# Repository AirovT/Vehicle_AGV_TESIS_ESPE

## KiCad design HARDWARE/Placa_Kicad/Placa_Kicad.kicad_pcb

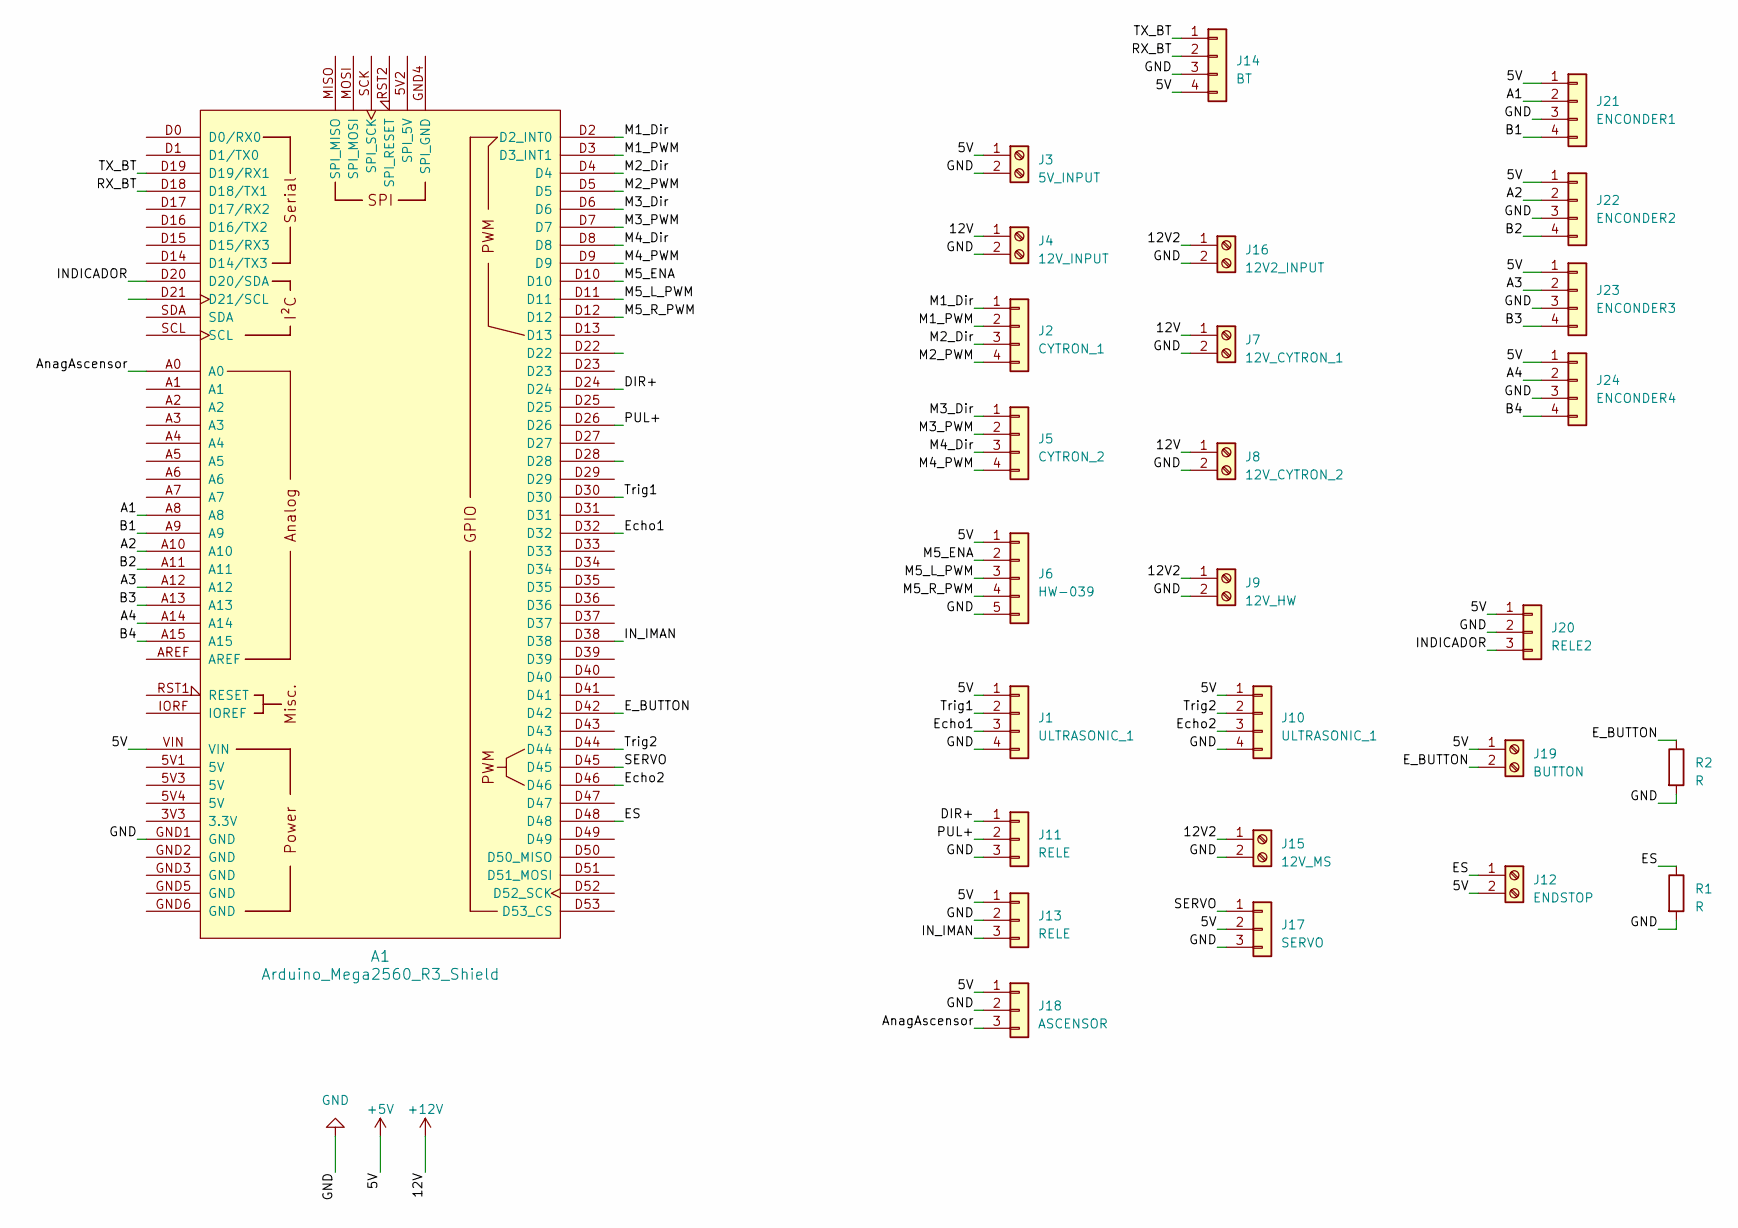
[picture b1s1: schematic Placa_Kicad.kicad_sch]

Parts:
A1: Arduino_Mega2560_R3_Shield
J1, J10: ULTRASONIC_1; JST_EH_B4B-EH-A_1x04_P2.50mm_Vertical
J2: CYTRON_1; JST_EH_B4B-EH-A_1x04_P2.50mm_Vertical
J3: 5V_INPUT; TerminalBlock_bornier-2_P5.08mm
J4: 12V_INPUT; TerminalBlock_bornier-2_P5.08mm
J5: CYTRON_2; JST_EH_B4B-EH-A_1x04_P2.50mm_Vertical
J6: HW-039; JST_EH_B5B-EH-A_1x05_P2.50mm_Vertical
J7: 12V_CYTRON_1; TerminalBlock_4Ucon_1x02_P3.50mm_Horizontal
J8: 12V_CYTRON_2; TerminalBlock_4Ucon_1x02_P3.50mm_Horizontal
J9: 12V_HW; TerminalBlock_4Ucon_1x02_P3.50mm_Horizontal
J11, J13: RELE; JST_EH_B3B-EH-A_1x03_P2.50mm_Vertical
J12: ENDSTOP; TerminalBlock_4Ucon_1x02_P3.50mm_Horizontal
J14: BT; JST_EH_B4B-EH-A_1x04_P2.50mm_Vertical
J15: 12V_MS; TerminalBlock_4Ucon_1x02_P3.50mm_Horizontal
J16: 12V2_INPUT; TerminalBlock_bornier-2_P5.08mm
J17: SERVO; JST_EH_B3B-EH-A_1x03_P2.50mm_Vertical
J18: ASCENSOR; JST_EH_B3B-EH-A_1x03_P2.50mm_Vertical
J19: BUTTON; TerminalBlock_4Ucon_1x02_P3.50mm_Horizontal
J20: RELE2; JST_EH_B3B-EH-A_1x03_P2.50mm_Vertical
J21: ENCONDER1; JST_EH_B4B-EH-A_1x04_P2.50mm_Vertical
J22: ENCONDER2; JST_EH_B4B-EH-A_1x04_P2.50mm_Vertical
J23: ENCONDER3; JST_EH_B4B-EH-A_1x04_P2.50mm_Vertical
J24: ENCONDER4; JST_EH_B4B-EH-A_1x04_P2.50mm_Vertical
R1, R2: R; R_Axial_DIN0204_L3.6mm_D1.6mm_P7.62mm_Horizontal

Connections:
+5V: A1.VIN, J1.1, J3.1, J6.1, J10.1, J12.2, J13.1, J14.4, J17.2, J18.1, J19.1, J20.1, J21.1, J22.1, J23.1, J24.1
+12V: J4.1, J7.1, J8.1
/12V2: J9.1, J15.1, J16.1
/A1: A1.A8, J21.2
/A2: A1.A10, J22.2
/A3: A1.A12, J23.2
/A4: A1.A14, J24.2
/AnagAscensor: A1.A0, J18.3
/B1: A1.A9, J21.4
/B2: A1.A11, J22.4
/B3: A1.A13, J23.4
/B4: A1.A15, J24.4
/DIR+: A1.D24, J11.1
/ES: A1.D48, J12.1, R1.1
/E_BUTTON: A1.D42, J19.2, R2.1
/Echo1: A1.D32, J1.3
/Echo2: A1.D46, J10.3
/INDICADOR: A1.D20 (D20/SDA), J20.3
/IN_IMAN: A1.D38, J13.3
/M1_Dir: A1.D2 (D2_INT0), J2.1
/M1_PWM: A1.D3 (D3_INT1), J2.2
/M2_Dir: A1.D4, J2.3
/M2_PWM: A1.D5, J2.4
/M3_Dir: A1.D6, J5.1
/M3_PWM: A1.D7, J5.2
/M4_Dir: A1.D8, J5.3
/M4_PWM: A1.D9, J5.4
/M5_ENA: A1.D10, J6.2
/M5_L_PWM: A1.D11, J6.3
/M5_R_PWM: A1.D12, J6.4
/PUL+: A1.D26, J11.2
/RX_BT: A1.D18 (D18/TX1), J14.2
/SERVO: A1.D45, J17.1
/TX_BT: A1.D19 (D19/RX1), J14.1
/Trig1: A1.D30, J1.2
/Trig2: A1.D44, J10.2
GND: A1.GND1 (GND), A1.GND2 (GND), A1.GND3 (GND), A1.GND5 (GND), A1.GND6 (GND), J1.4, J3.2, J4.2, J6.5, J7.2, J8.2, J9.2, J10.4, J11.3, J13.2, J14.3, J15.2, J16.2, J17.3, J18.2, J20.2, J21.3, J22.3, J23.3, J24.3, R1.2, R2.2

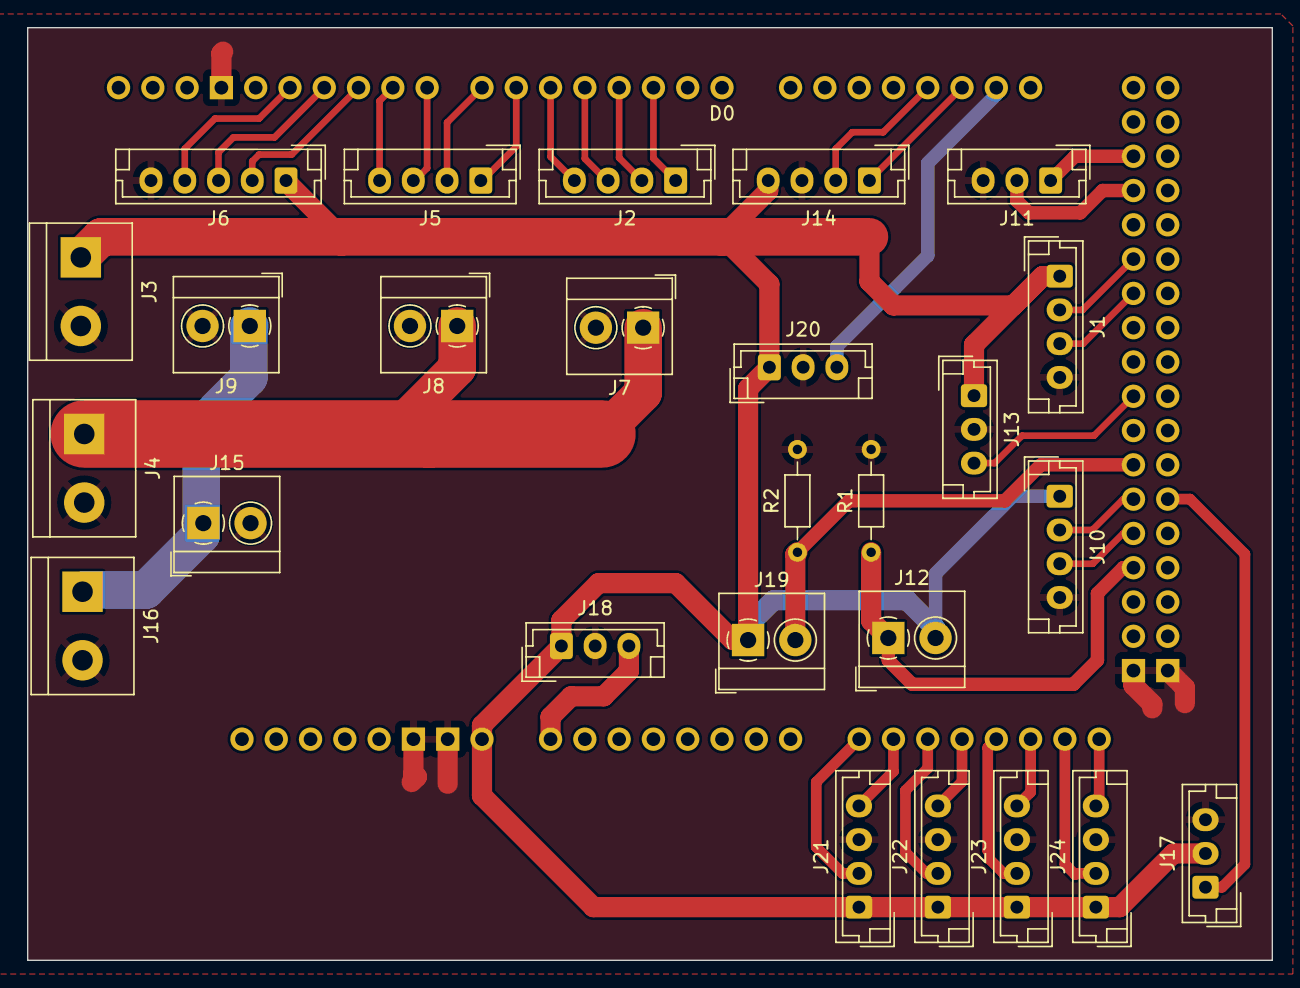
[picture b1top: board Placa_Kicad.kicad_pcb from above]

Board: 2 copper layers, 92.2 x 69.1 mm, 27 parts (0 on the bottom side), 37 nets.

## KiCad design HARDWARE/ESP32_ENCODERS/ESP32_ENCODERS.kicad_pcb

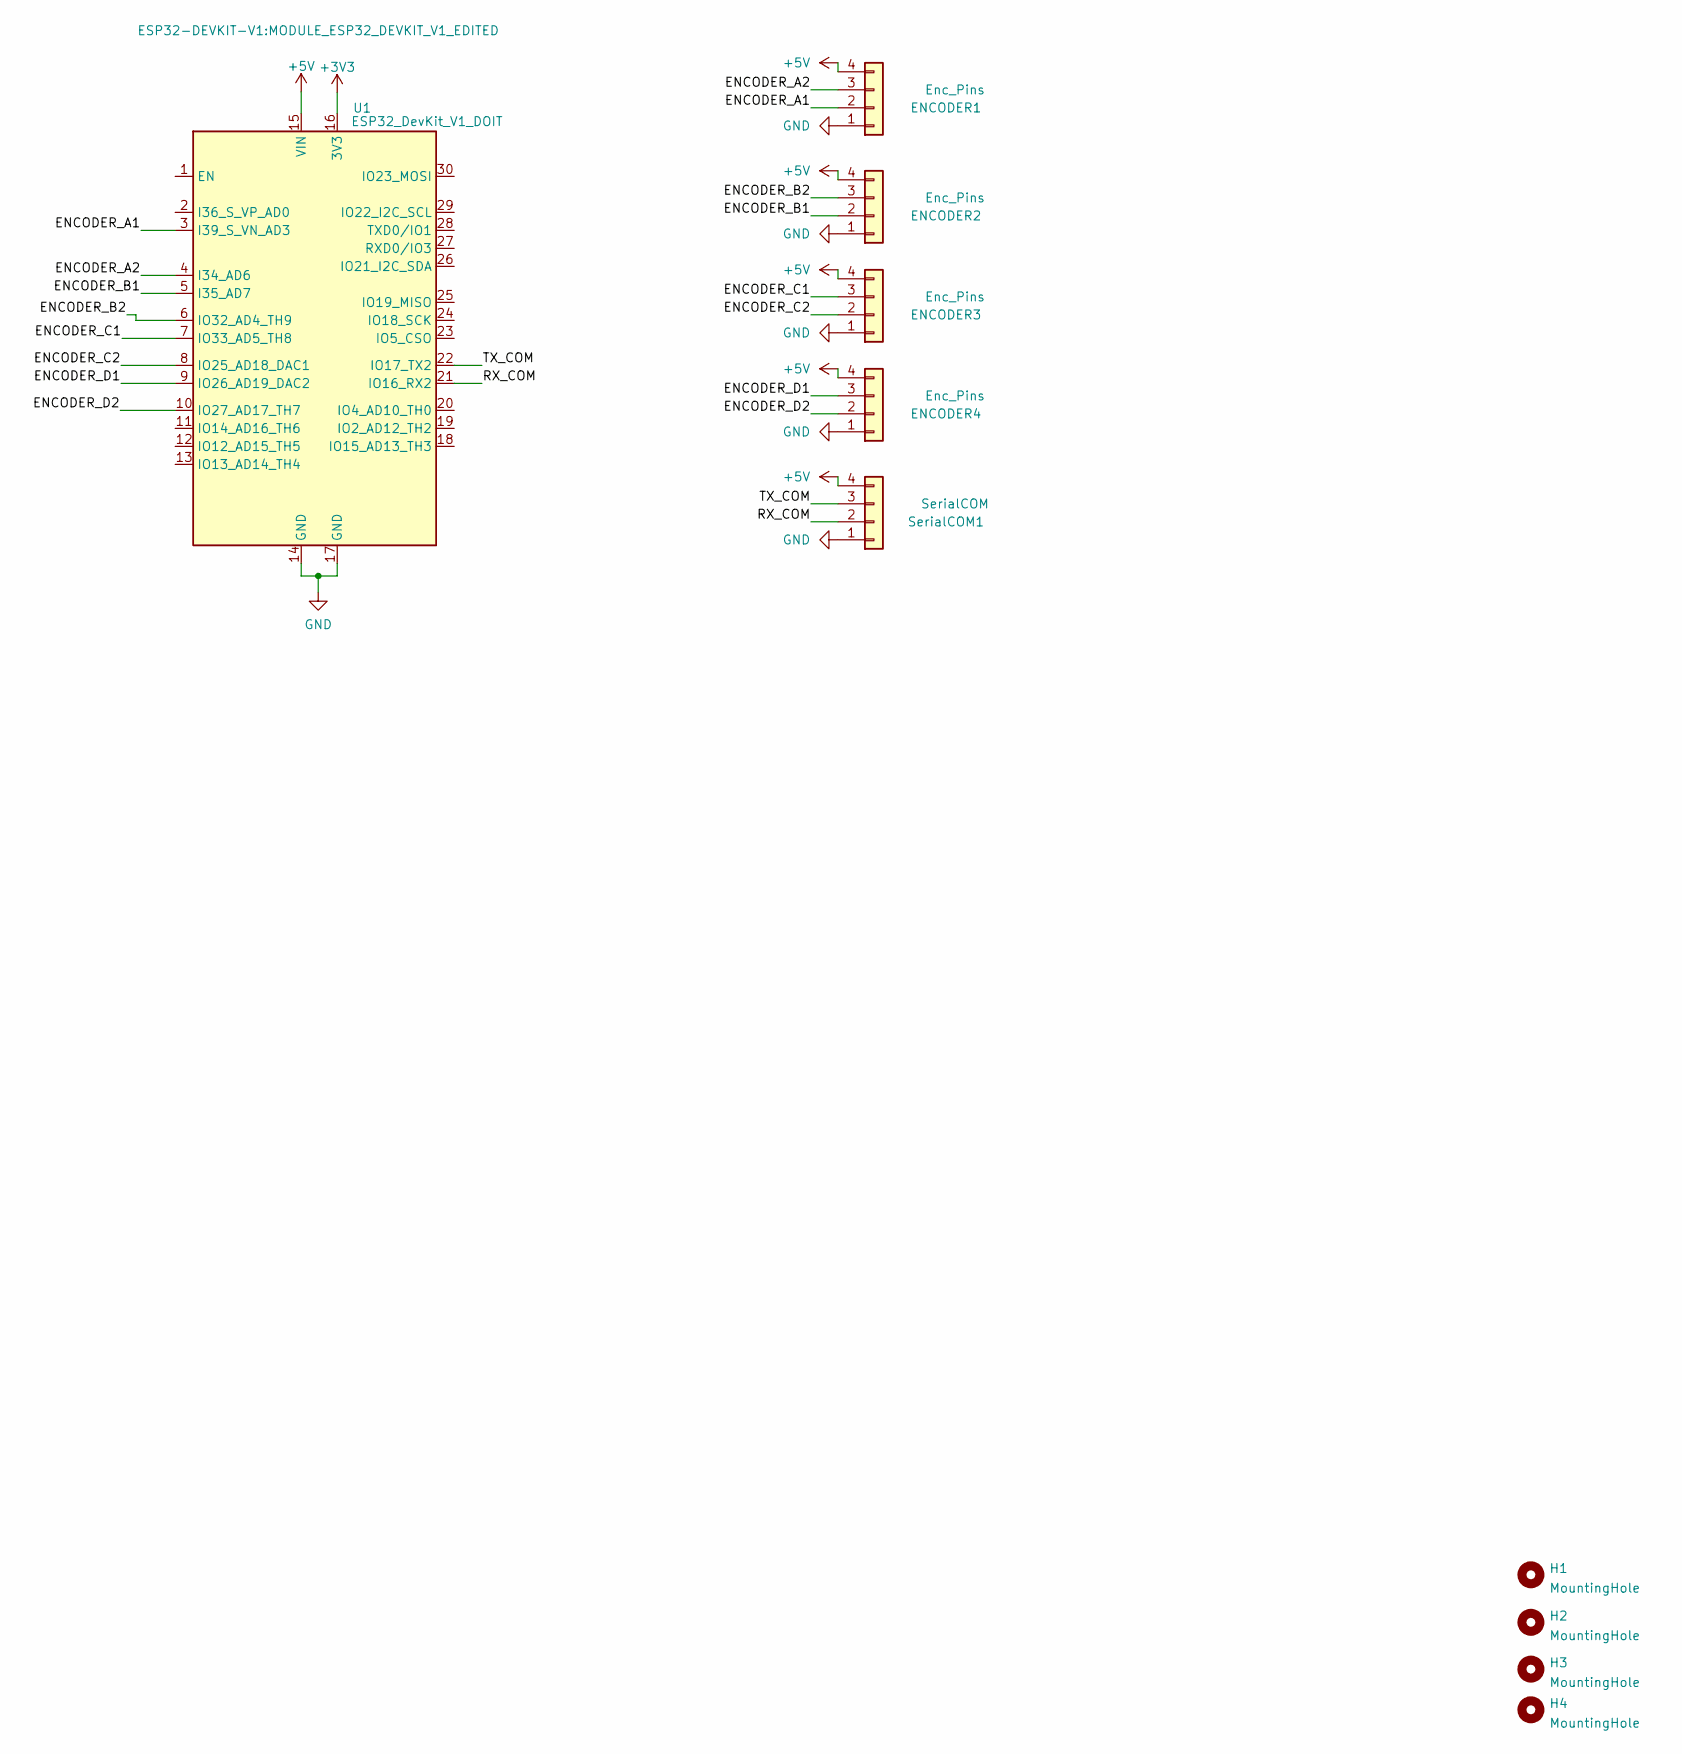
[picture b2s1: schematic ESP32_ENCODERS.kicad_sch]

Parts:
ENCODER1, ENCODER2, ENCODER3, ENCODER4: Enc_Pins; JST_EH_S4B-EH_1x04_P2.50mm_Horizontal
H1, H2, H3, H4: MountingHole; MountingHole_2.2mm_M2_DIN965_Pad
SerialCOM1: SerialCOM; JST_XA_B04B-XASK-1_1x04_P2.50mm_Vertical
U1: ESP32_DevKit_V1_DOIT; MODULE_ESP32_DEVKIT_V1_EDITED

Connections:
+3V3: U1.16 (3V3)
+5V: ENCODER1.4, ENCODER2.4, ENCODER3.4, ENCODER4.4, SerialCOM1.4, U1.15 (VIN)
/ENCODER_A1: ENCODER1.2, U1.3 (I39_S_VN_AD3)
/ENCODER_A2: ENCODER1.3, U1.4 (I34_AD6)
/ENCODER_B1: ENCODER2.2, U1.5 (I35_AD7)
/ENCODER_B2: ENCODER2.3, U1.6 (IO32_AD4_TH9)
/ENCODER_C1: ENCODER3.3, U1.7 (IO33_AD5_TH8)
/ENCODER_C2: ENCODER3.2, U1.8 (IO25_AD18_DAC1)
/ENCODER_D1: ENCODER4.3, U1.9 (IO26_AD19_DAC2)
/ENCODER_D2: ENCODER4.2, U1.10 (IO27_AD17_TH7)
/RX_COM: SerialCOM1.2, U1.21 (IO16_RX2)
/TX_COM: SerialCOM1.3, U1.22 (IO17_TX2)
GND: ENCODER1.1, ENCODER2.1, ENCODER3.1, ENCODER4.1, SerialCOM1.1, U1.14 (GND), U1.17 (GND)

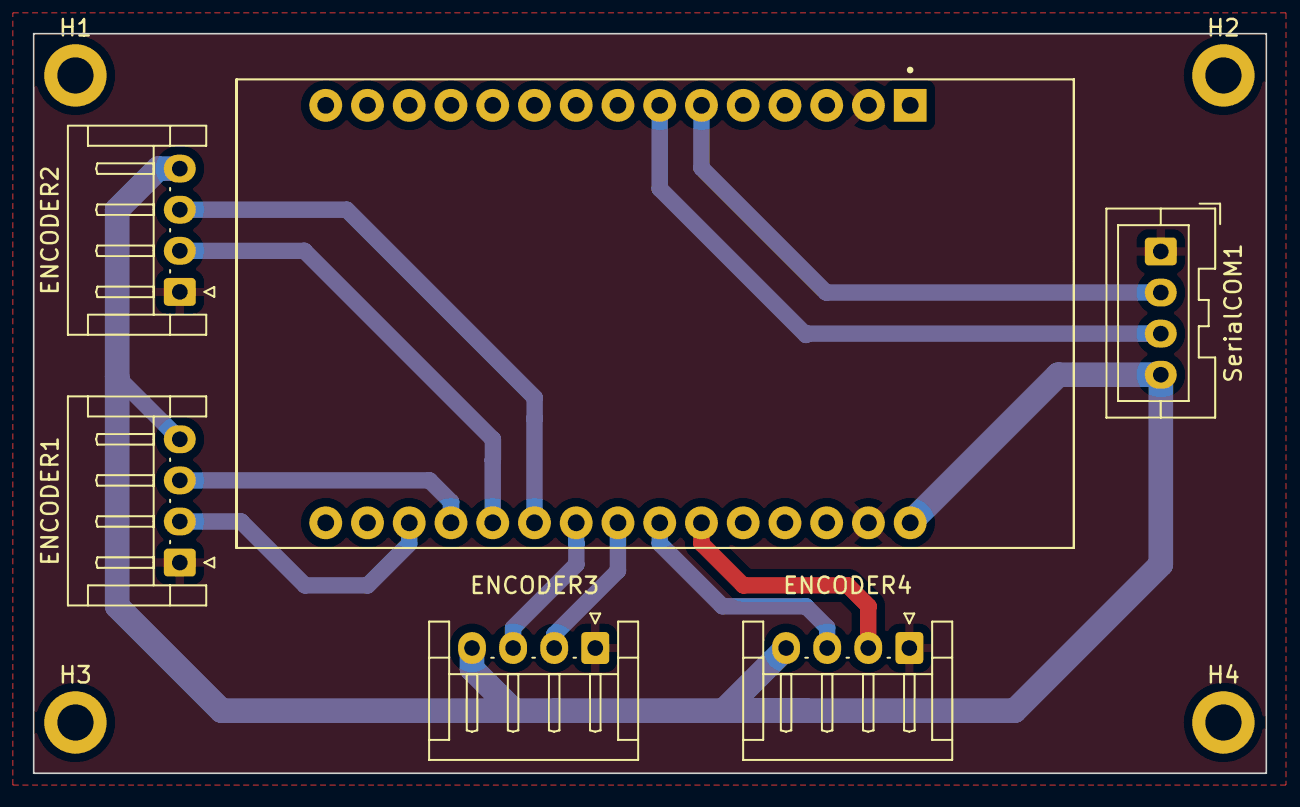
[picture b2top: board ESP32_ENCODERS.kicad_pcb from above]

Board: 2 copper layers, 75.0 x 45.0 mm, 10 parts (0 on the bottom side), 12 nets.

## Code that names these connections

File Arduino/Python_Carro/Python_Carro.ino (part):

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//////////////////////////////

// ========= MOTORES MOVIMIENTO =============//
#define M1_Dir 2
#define M1_Vel 3

#define M2_Dir 4
#define M2_Vel 5

#define M3_Dir 6
#define M3_Vel 7

#define M4_Dir 8
#define M4_Vel 9

String mensaje, m1_vel, m2_vel, m3_vel, m4_vel;
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
#define IMAN 38

#define SERVO_PIN 13
#define ENDSTOP 52

// Define height and maximum height
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// bool EndStop;

//========= ULTRASONIC ========//
#define TRIG1 30
#define ECHO1 32

#define TRIG2 44
#define ECHO2 46

int Distance1;
int Distance2;
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  Serial.begin(115200);
  Serial1.begin(115200);

  pinMode(M1_Dir, OUTPUT);
  pinMode(M1_Vel, OUTPUT);

  pinMode(M2_Dir, OUTPUT);
  pinMode(M2_Vel, OUTPUT);

  pinMode(M3_Dir, OUTPUT);
  pinMode(M3_Vel, OUTPUT);

  pinMode(M4_Dir, OUTPUT);
  pinMode(M4_Vel, OUTPUT);

  //====================
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   // Configurar el pin del endstop como entrada
  pinMode(ENDSTOP, INPUT_PULLUP); // Utiliza un pull-up interno para evitar ruido

    myServo.attach(SERVO_PIN);  // Conecta el servo al pin 9
    setServoAngle(90);  // Establece el ángulo del servo a 0 grados

 
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


    pinMode(TRIG1, OUTPUT);
  pinMode(ECHO1, INPUT);
  
  // Inicializar pines del segundo sensor ultrasónico
  pinMode(TRIG2, OUTPUT);
  pinMode(ECHO2, INPUT);


} 
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
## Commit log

2024-12-17 cambios
2024-12-17 cambios2
2025-01-09 https://github.com/AirovT/Vehicle_AGV_TESIS_ESPE.git
2025-01-10 Envio de datos modificados
2025-01-16 Varias Actualizaciones
2025-01-20 Revert "Merge commit 'bc45bd58c058deae2172303bbcf6e99ff63005d9'"
    This reverts commit d5a0b124aff9bd6bd29f66b29f358de85c0094ca, reversing
    changes made to 14d741a9daa2ab2edc39f48dd2134658798e8950.
2025-01-21 reparacion envio
2025-01-21 Actualizar todos los archivos
2025-01-25 Reparaciones Generales
2025-02-02 Cambios Automatico
2025-02-02 Encoder Actualizado
2025-02-04 BANDERAS FUNCIONALES - Git Ignore imagenes Calibracion
2025-02-04 Banderas Funcionales y gitignore
2025-02-05 Nuevo sistema de estimacion - Beta1
2025-02-05 ESTIMACION FUNCIONAL. PASO A SIGUIENTES ETAPAS DE PRUEBA
